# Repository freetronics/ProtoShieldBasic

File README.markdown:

Freetronics Basic ProtoShield
==============================
Copyright 2010 Jonathan Oxer <jon@freetronics.com>  
Practical Arduino: <www.practicalarduino.com>  
Freetronics: <www.freetronics.com>

A minimalist, general-purpose prototyping shield for the Arduino
Duemilanove microcontroller and other boards based on the same header
format, such as the TwentyTen, Seeeduino, and Arduino Pro.

This design is intended to maximise prototyping area by extending the
plain pads right to the ends of the board, which also makes it easier
to fit horizontal PCB-mount sockets that need to overlap the edge.

Features:

 * Pads for reset button connected to Arduino reset pin.
 * Pads for two 100nF smoothing capacitors.
 * Pads for "power on" LED and current-limiting resistor.
 * Header labels on both the top and the bottom so you can see what you
   are connecting without having to keep turning the board over.

INSTALLATION
------------
The design is saved as an EAGLE project. EAGLE PCB design software is
available from www.cadsoftusa.com free for non-commercial use. To use
this project download it and place the directory containing these files
into the "eagle" directory on your computer. Then open EAGLE and
navigate to Projects -> eagle -> ProtoShield.

LICENSE
-------
Licensed under the TAPR Open Hardware License (www.tapr.org/OHL).

FABRICATION OPTIONS
-------------------
If you haven't had PCBs fabricated before it can be very confusing
trying to work out all the options. We have some of our boards fabbed
by pcbcart.com, so to save you some hassle the list below shows our
recommended selections for the options on their order form. Some of the
settings can be changed if you have different preferences but this is a
sensible starting point if you don't know what the options mean and
should result in a decent board.

Note that the colour options below are for a yellow board with black
text, and with all exposed surfaces gold-plated for maximum durability.

 * Material:                 FR4
 * Layers:                   2 Layer
 * Material Details:         Standard Tg 140C
 * Part Number:              PROTOSHIELD-BASIC (or substitute your own)
 * Board Type:               Single Unit
 * Board Size (width):       59.69mm
 * Board Size (height):      53.34mm
 * Quantity:                 Select as appropriate
 * Thickness:                1.2mm
 * Surface Finish:           ENIG (gold)
 * Copper Weight (Finished): 35um
 * Min. Tracing/Spacing:     0.20mm    (8 thou)
 * Min. Annular Ring:        0.30mm    (12 thou)
 * Smallest Holes:           0.40mm
 * Holes Numbers:            300-600
 * Surface Mount:            1 side
 * Soldermask:               Both sides
 * Peelable Soldermask:      None
 * Soldermask Color:         Yellow
 * Matt Color:               None
 * Silkscreen Legend:        2 sides
 * Silkscreen Legend Color:  Blue
 * Gold Fingers:             No
 * Gold Fingers Number:
 * Gold Fingers Chamfer:
 * Slots in Board:           No Slot in Board
 * Slots quantity in board:
 * Testing:                  Yes
 * UL Marking:               No
 * Date Code Marking:        No
 * Lead Time:                8 or 12 days, as you prefer (8 costs a small amount more)
 * Special Requirement Note: PCB is routed to outside of thin Dimension line on Top layer

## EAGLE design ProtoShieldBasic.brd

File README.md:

Freetronics ProtoShieldBasic
==============================
Copyright 2013 Freetronics Pty Ltd  
Freetronics site:  www.freetronics.com  
Freetronics email: info@freetronics.com  

A minimalist general-purpose prototyping shield for the Arduino
Uno, Freetronics Eleven, and other compatible boards based on the same
header format.

This design is intended to maximise prototyping area by extending the
plain pads right to the ends of the board, which also makes it easier
to fit horizontal PCB-mount sockets that need to overlap the edge.

Note that this design is intended for simple fabrication and assembly,
and does not have many of the features of other prototyping shields
such as the "ProtoShield Pro" (also available from Freetronics) such as
general-purpose LEDs.

Features:

 * Pads for reset button connected to Arduino reset pin.
 * Pads for 100nF smoothing capacitor.
 * Pads for "power on" LED and current-limiting resistor.
 * Parts overlay on both the top and the bottom so you can see what you
   are connecting without having to keep turning the board over.

More information is available at:

  http://www.freetronics.com/psb

INSTALLATION
------------
The design is saved as an EAGLE project. EAGLE PCB design software is
available from www.cadsoftusa.com free for non-commercial use. To use
this project download it and place the directory containing these files
into the "eagle" directory on your computer. Then open EAGLE and
navigate to Projects -> eagle -> ProtoShieldBasic.

DISTRIBUTION
------------
The specific terms of distribution of this project are governed by the
license referenced below.

LICENSE
-------
Licensed under the TAPR Open Hardware License (www.tapr.org/OHL).
The "license" folder within this repository also contains a copy of
this license in plain text format.

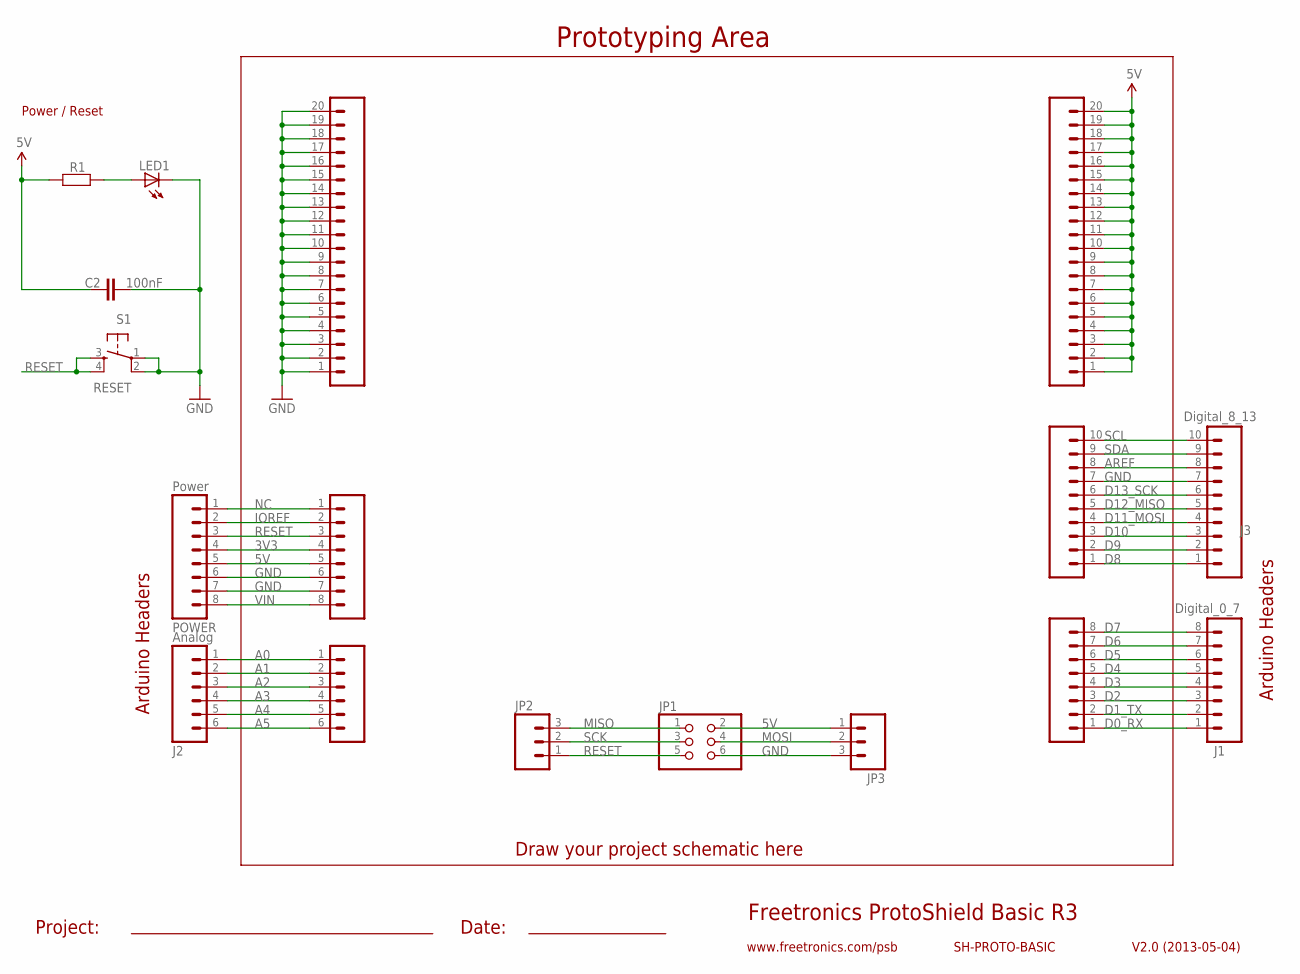
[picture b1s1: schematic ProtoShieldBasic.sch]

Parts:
C2: 100nF; CAP-PTH-SMALL
J1: Digital_0_7; 1X08
J2: Analog; 1X06
J3: Digital_8_13; 1X10
JP1: PINHD-2X3; 2X03
JP2, JP3: M03PTH; 1X03
LED1: LED3MM
PADS_5V: M20; 1X20
PADS_GND: M20; 1X20
POWER: Power; 1X08
R1: RESISTORPTH1; AXIAL-0.3
S1: RESET; TACTILE-PTH
SL1: Digital_0_7; 1X08
SL2: Analog; 1X06
SL3: Digital_8_13; 1X10
SLP: Power; 1X08

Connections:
3V3: POWER.4, SLP.4
5V: C2.1, JP1.2, JP3.1, PADS_5V.1, PADS_5V.2, PADS_5V.3, PADS_5V.4, PADS_5V.5, PADS_5V.6, PADS_5V.7, PADS_5V.8, PADS_5V.9, PADS_5V.10, PADS_5V.11, PADS_5V.12, PADS_5V.13, PADS_5V.14, PADS_5V.15, PADS_5V.16, PADS_5V.17, PADS_5V.18, PADS_5V.19, PADS_5V.20, POWER.5, R1.P$1 (1), SLP.5
A0: J2.1, SL2.1
A1: J2.2, SL2.2
A2: J2.3, SL2.3
A3: J2.4, SL2.4
A4: J2.5, SL2.5
A5: J2.6, SL2.6
AREF: J3.8, SL3.8
D0_RX: J1.1, SL1.1
D1_TX: J1.2, SL1.2
D2: J1.3, SL1.3
D3: J1.4, SL1.4
D4: J1.5, SL1.5
D5: J1.6, SL1.6
D6: J1.7, SL1.7
D7: J1.8, SL1.8
D8: J3.1, SL3.1
D9: J3.2, SL3.2
D10: J3.3, SL3.3
D11_MOSI: J3.4, SL3.4
D12_MISO: J3.5, SL3.5
D13_SCK: J3.6, SL3.6
GND: C2.2, J3.7, JP1.6, JP3.3, LED1.K (C), PADS_GND.1, PADS_GND.2, PADS_GND.3, PADS_GND.4, PADS_GND.5, PADS_GND.6, PADS_GND.7, PADS_GND.8, PADS_GND.9, PADS_GND.10, PADS_GND.11, PADS_GND.12, PADS_GND.13, PADS_GND.14, PADS_GND.15, PADS_GND.16, PADS_GND.17, PADS_GND.18, PADS_GND.19, PADS_GND.20, POWER.6, POWER.7, S1.1, S1.2, SL3.7, SLP.6, SLP.7
IOREF: POWER.2, SLP.2
MISO: JP1.1, JP2.3
MOSI: JP1.4, JP3.2
unnamed: LED1.A, R1.P$2 (2)
NC: POWER.1, SLP.1
RESET: JP1.5, JP2.1, POWER.3, S1.3, S1.4, SLP.3
SCK: JP1.3, JP2.2
SCL: J3.10, SL3.10
SDA: J3.9, SL3.9
VIN: POWER.8, SLP.8

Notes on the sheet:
Freetronics ProtoShield Basic R3
V2.0 (2013-05-04)
www.freetronics.com/psb
SH-PROTO-BASIC
Prototyping Area
Arduino Headers
Power / Reset
Project:
Date:
Draw your project schematic here

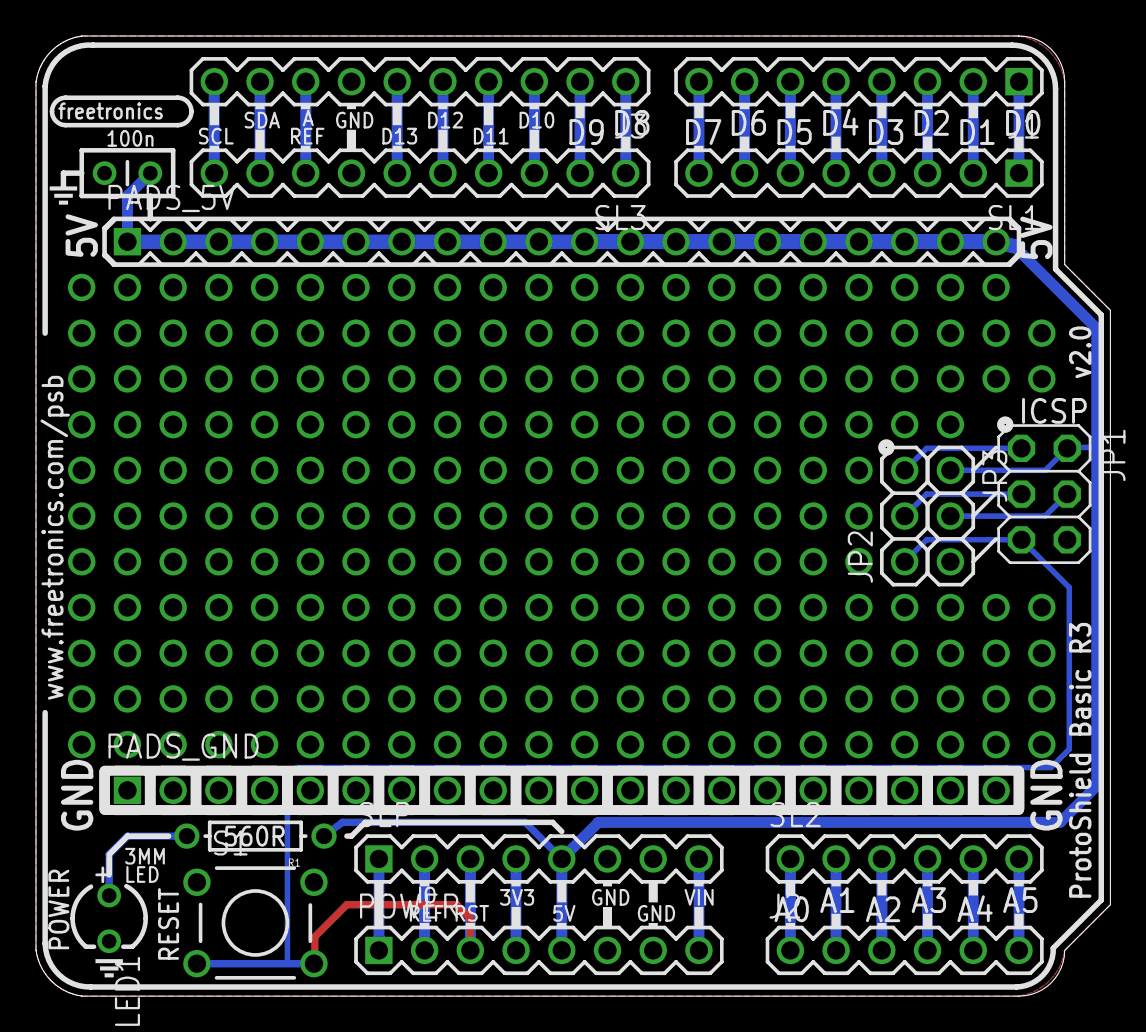
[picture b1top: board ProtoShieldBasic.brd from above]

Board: 2 copper layers, 59.7 x 53.3 mm, 17 parts (0 on the bottom side), 34 nets.

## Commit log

2010-05-09 Initial version of project
2010-05-10 Simplified schematic and adjusted routing
2010-05-10 Added preview image
2010-05-10 Fixed location of 100n label
2010-05-10 Updated README to reflect part positions provided on the PCB
2010-05-10 Trivial tweaks to track sizes
2010-05-10 Fixed positions of misplaced net labels
2010-05-10 Updated Eagle project file for v5.9.0
2010-05-10 Removed irrelevant copied content from ProtoShield0603 README
2010-05-10 Added details on fabrication options
2010-05-10 Minor colour change in gerbv project file
2010-05-10 Updated preview image
2010-05-12 Updated Eagle project file
2010-05-12 Added second decoupling cap and reduced length of power rails
2010-05-12 Switch position of power rails and updated routing
2010-05-14 Trivial tweaks to overlay
2010-05-14 Deleted old preview image
2010-05-14 Added new preview image
2010-05-20 Updated CHANGES prior to fab
2010-05-20 Tiny tweak to overlay position
2010-05-20 Updated document name and version
2010-05-20 Updated README to reference 2 smoothing caps
2010-05-27 Removed obsolete production files
2010-05-27 Renamed README
2010-05-27 Minor updates
2010-05-27 Moved license into subdir
2010-05-27 Removed obsolete files
2010-05-27 Moved preview image into docs dir
2010-05-28 Updated format of README file to match Freetronics standards
2010-05-28 Fixed project name in README
2010-06-01 Generalised part designators
2010-06-01 Replaced preview image
2010-06-01 Added PDF of schematic
2010-06-02 sch url edit
2010-06-02 pcb artwork edit
2010-06-02 Restructured schematic as a worksheet template
2010-06-02 Increased label sizes on overlay
2010-06-02 Adjusted position of prototyping area
2010-06-02 Overlay text on RHS made a little larger
2010-06-02 Moved supporting parts to left side of schematic
2010-06-03 Release candidate
2010-06-26 Fixed product page URL and number of smoothing caps
2012-02-01 Updated headers to R3 format
2013-06-04 Release v2.0 with R3 headers

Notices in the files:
ProtoShieldBasic.brd:
(c) 2013 Freetronics
